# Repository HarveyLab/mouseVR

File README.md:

# Harvey Lab Mouse VR
Developed by members of the Harvey Lab (http://harveylab.hms.harvard.edu/) and the HMS Research Instrumentation Core (http://instrumentation.hms.harvard.edu/). Community contributions to any aspects of the designs or documentation very welcome, please submit a pull request with a clear description of the changes/additions and the rationale behind them.

## Table of Contents

1. [Overview](#overview)
2. [Main Components](#main-components)
3. [Getting started](#getting-started)
4. [Build Guide](#build-guide)
5. [Screen Assembly](#screen-assembly)
6. [Ball Cup Assembly](#ball-cup-assembly)
7. [Ball Sensor Software](#ball-sensor-software)
8. [Reward system](#reward-system)
9. [Behavior PCB Overview](#behavior-pcb-overview)
10. [Software](#software)
11. [Headfixation](#headfixation)
12. [FAQs](#faqs)
13. [Appendix](#appendix)

## Overview

### Main components
Harvey Lab miniaturized mouse VR rig for virtual navigation and decision-making tasks

The VR setup is comprised of several independent assemblies:

1. **The screen assembly:** a laser projector projects onto a parabolic screen surrounding the mouse. This is the basis for the visual virtual reality.

2. **Ball cup assembly:** an air-supported 8" styrofoam ball that the mouse can run on, with associated ball cup, sensors, and electronics

3. **Reward delivery system and lick sensor:** lick spout, liquid reward reservoir, solenoid, and associated electronics

4. **Enclosure:** A box surrounding the behavioral setup.

Each of these components is independent of the others: i.e. just the screen could be used in combination with a different treadmill and reward delivery system. The electronics for the ball sensors, reward delivery, and lick detection are all mounted on the same PCB. If only one or two of these functions are needed, you do not need to populate the entire PCB.

The screen assembly is designed to be small enough to be mounted within a standard 19" server rack, which could easily fit 3 rigs stacked vertically (or two + monitor and keyboard station). 

Screen and ball cup assemblies:

### Getting started

All the parts for the assemblies are listed in this google sheet: https://docs.google.com/spreadsheets/d/1hkXaeRBd7GJPuhIFjeKkEIziQik9mlkZpzjhxGrkA7A/edit?usp=sharing 

The build guide (below) contains detailed schematics of the various assemblies, **as well as additional notes about part requirements and alternative parts**. 

### Getting help

Open an issue. We will do our best to support hardware-related issues and correct errors or update documentation where things are unclear. Issues related to the design and execution of virtual environments (for example running ViRMEn code) is currently beyond the scope of this repository. 

### Contributing

We welcome contributions including, but not limited to, hardware improvements, example code for hardware interfacing, and refinements to our documentation. Please submit your contributions through a pull request.

# Build Guide

## Projector

Update 2021-02-18: 

This back projection screen assembly was originally designed for use with the Celluon Picobit laser projector (released in 2016). This projector (along with our recommended alternative laser projectors) has been discontinued and Celluon no longer produces laser projectors. The advantage of laser projectors is that they can project onto a curved surfaces with the image in focus across the entire surface. We can no longer recommend these however due to their inavailability.

We now recommend using the Texas instruments LightCrafter DLP 3010 EVM:  https://www.ti.com/tool/DLPDLCR3010EVM-G2. The DLP 2010 may also work. The back-projection enclosure has now been adapted for the DLP 3010, with a 3D-printed part holding the projector at a downward angle above the top acrylic piece to account for the upward projection angle. See the acrylic design files suffixed with "DLP_mount" and the "DLP_mount_quarter20" Inventor and STL files for the 3D-printed part, which can be mounted on the top acrylic piece with two 1/4-20 screws.

**Note 1**: The side acrylic pieces in vrRig_laserCutter_allParts_DLP_mount are also modified - they are 2 inches shorter than in the original design, and the slots for the mirrors are moved (only in the y direction). 

**Note 2**: You may have to widen the slot in the 3D-printed part by a fraction of a millimeter to account for projector manufacturing errors. The total width should be 0.4 mm wider than the width of the projector base. The design width of the base is 135.0 mm; you can measure yours with a caliper. If it fits correctly, the projector should slide in under the lips such that it is flat against the base and flush with the back of the mount.

The LightCrafters will be supported for longer than typical consumer projectors, have greater programmability, and have some some nice user features such as the ability to easily display calibration images and independently shut off Red green and blue LEDs in the software, which could be great for imaging applications - getting rid of that hard-to-block red light without a filter. Some groups have also added LEDs of desired wavelength - for example UV (this was using DLP3010). They also have fairly low input lag: from coarse tests it appears to be comparable to a standard dell desktop monitor (5-15 ms), although if this is important for you please conduct your own tests. 

The differences in focus across the screen are fairly subtle even to the human eye, so we do not expect this to impact visually-guided navigation or studies of mouse visual responses. Please see appendix for pictures of a modified screen assembly used with a DLP3010 (Oleksandr Radomskyi, Santiagio Rompani Group, EMBL, Rome). 

Thanks to Oleksandr Radomskyi and Santiagio Rompani for sharing information about using Lightcrafters with these designs. 

OLD INFO - see update above:

The projector should be a laser projector so that the image is in focus across the entire curvature of the screen. In terms of laser projectors compatible with this design, we like the Celluon PicoPro, Celluon PicoBit, or the LaserBeamPro (in that order of preference). The LaserBeamPro can exhibit burn-in.
Avoid the Sony portable laser projector due to lag. The projector throw ratio matters: get one with 1.4:1 (pretty standard for
the small laser projectors). Projectors with greater divergence will work as well. Get a projector that projects straight out i.e.
the light for the horizontal center line of the projected image should be at the same elevation as the body of the projector.
Some projectors (especially short throw) are designed to project upwards from a table or desk, this will not work with the
setup.

If you wish to use DLP projectors, we've done some basic testing of them but have not trained mice with them. The image is slightly out of focus in certain places, but it is not a serious issue. The main issue with DLP projectors is that most do not project straight out of the projector - they project slightly upwards with build in keystone correction. This has two main effects. First, the projector will need to be mounted at a slight angle relative to the top piece of the VR setup (ask Noah if this isn't clear). Second, due to the keystone correct and the angle of mounting, the transformation functions will need to be adjusted appropriately within whatever VR software you are using (if you wish to know exactly where on the screen things are being displayed). The MEX-file `fliptransform_parab_dlp_w_offset` provided under `Software/Virmen/transformations` may work for this purpose.

**Note that the laser cut mount for the projector included in these designs is specifically for the PicoBit.** It will also work with the PicoPro and laser beam pro if you remove the top "alignment" piece and stick the projector to the bottom piece using double sided tape or velcro (the height and geometry works, you will just need to center the image by eye when you stick down the projector). 

If you want to test out a DLP projection with this design, this projector: https://www.amazon.com/dp/B078PC1QS5/ref=sspa_dk_detail_5?psc=1 has the right throw. I'm not sure if it projectes straight out from the projector or slightly upwards. Parts of the projected image will be out of focus due to projecting onto a curved surface, but this might not be so bad for the mouse. If you do try it, let us know how it works!

## Screen Assembly

### Parts list and notes

The parts are listed in the "screen assembly" section of the parts list google doc: https://docs.google.com/spreadsheets/d/1hkXaeRBd7GJPuhIFjeKkEIziQik9mlkZpzjhxGrkA7A/edit?usp=sharing 

#### Mirrors

These should be approximately 1/4" thick and first surface if possible. Non first surface mirrors will result in some double
image "ghosting" but otherwise will work with the design. Acrylic mirrors can be used to save money and time - these can
easily be laser cut. Note that acrylic mirrors typically do not have surfaces as smooth as glass and the projected image may
appear textured as a result.

#### Rails, brackets, and t-nuts

McMaster or Thorlabs or any other 80-20 style rail materials should work. Note that Mcmaster t-nuts / fasteners are not
compatible with thorlabs rails as they have slightly different slot dimensions. Thorlabs t-nuts are compatible with McMaster t-slotted framing. Only the 15" Horizontal rails need to be 1/4-20 end tapped.

#### Acrylic

Any 1/4" acrylic that can be easily laser cut should work fine. It does not need to be matte or black. Opaque acrylic is best to block stray light. Stray light and reflections can also be blocked on any type of acylic using pieces of the black flocked self adhesive paper 

### Part Preparation

These steps will take approximately one hour.

For part preparation you will need the following equipment:

• Power drill

• 1/4-20 thread cutting tap

• Laser cutter with at least 12 x 24" bead, power to cut through 1/4 inch acrylic. (There are online services that will do this cutting for you if you don't have access to a laser cutter. We've been quoted around $400 for cutting these designs, although there may be cheaper options).

Steps:
**1. Laser cut the parts.** The file you should need is https://github.com/HarveyLab/mouseVR/blob/master/Hardware/BackProjection/vrRig_laserCutter_allParts.pdf. (NOTE: for the DLP 3010 projector, use https://github.com/HarveyLab/mouseVR/blob/master/Hardware/BackProjection/vrRig_laserCutter_allParts_DLP_mount.pdf instead.) The scale in the document should be 1:1, inch units, but a small 1x1" scale square is included. Ensure that it is 1" on each side, and scale parts uniformly if necessary. Arrange the parts for cutting. eg, for cutting on two 18 x 32" pieces of acrylic:

**2. Tap holes in the laser cut parts.** All round holes in the laser cut parts are either 0.26" through holes, or 0.2-0.21 holes
that should be 1/4-20 tapped. It is safe to assume that if a 1/4-20 screw does not fit through it, it should be tapped. Refer
to the parts drawings if you are unsure. Don’t worry about tapping perfectly perpendicular to the face of the acrylic - we
use a hand drill and eyeball it and that works fine for us. Use a blade to clear out waste acrylic from the parabola-shaped
screen slots in the top and bottom pieces.

**3. Cut screen film to size:** Using a ruler and a pair of scissors, cut out a rectangular piece that is approximately 21.3 x 12
inches.

4. If using McMaster rails or 80-20 that needs to be cut to length, cut 4 pieces 18" in length for the legs, and 2 pieces 15"
in length for the cross braces. Hand tap the ends of 15" pieces with the 1/4-20 thread cutting tap.

**5. If using self-adhesive black flocked paper, cut two ~ 7.5 x 4" pieces.**

### Assembly

Assembly takes approximately one hour.

Refer to the figure below for a visual guide.

Steps:

**1. Add corner brackets to the bottom piece.** Place the bottom piece (parabolic screen slot, no holes or cutout in center) flat on the table and screw four 1" brackets into it as illustrated using 3/8"-long low profile screws.

**2. Attach sides** using the 1" brackets and 3/8"-long low profile screws. The long flat edges of the sides should be on
the bottom. Stick the cut black-flocked paper / felt pieces to the inside of the sides closest to the screen. Attach four
more 1" brackets as illustrated.

**3. Attach top piece.** Screw into place from the inside using the 1" brackets and 3/8"-long low profile screws.

**4. Assemble the projector mount.** To make sure that you aren’t messing it up, screw the
projector onto the larger of the two pieces using a 3/8"-long 1/4-20 screw through the center hole in the base mount into
the threaded hole on the bottom of the projector. Make sure it is in the orientation such that the fan on the bottom of
the projector is fully visible through the cutout in the acrylic (you may need to flip the acrylic base over). Screw the top
piece of the mount into place as illustrated and then attach the entire thing to the screen assembly using 1/2" (or longer)
1/4-20 screws.

**5. Join the two sides with the end-tapped 15" rails.** Ensure that you are using the right holes and not the holes reserved for
the legs (arranged in vertical pairs 1" apart).

**6. Flip the assembly over. Insert each leg into place**, attaching it to the inside of the assembly using t-nuts or fasteners (see
this note). **Set the height of the screen by adjusting the length that each leg sticks out of the box.**
Attach the right angle brackets to the base of each leg using t-nuts /fasteners.

**7. Repeat for all four legs.** Use a ruler or measuring tape to ensure that all legs are the same height.

**8. If using the acrylic base, attach to the right angle brackets** using 3/8"-long low profile screws. The part of the base that
connects the two sides should be at the back of the assembly, away from the screen.

**9. Flip the assembly upright.** If you are assembling in its final position, bolt the screen assembly down to a breadboard or
air table and insert the two mirrors. Put tape of pieces of black flocked adhesive paper over the openings in the sides to
prevent the mirrors from slipping out. **CRITICAL STEP: the glass first surface mirrors come with a blue protective film
on the coated side. Remove this film and ensure that the coated side ("first surface") is facing towards the screen.** Both
sides will appear reflective but only one side has the reflective coating.
If you plan on moving the assembly, skip this step and insert the mirrors once it is in its final position.

**10. Slide the screen into the parabola-shaped slots.** If it does not fit, there may be waste acrylic stuck in these slots - this
can be easily removed with a box cutter or other blade. cutting a slight V into one of the horizontal edges of the screen
can help with insertion. Once the screen is in place, use binder clips, tape, or glue along the top edge to secure it. Trim away excess screen. We also often apply black tape along the vertical edges of the screen to stick it
to the sides of the box and block out stray light from the projector.

## Ball cup assembly

### Parts list and notes

The parts are listed in the "screen assembly" section of the parts list google doc: https://docs.google.com/spreadsheets/d/1hkXaeRBd7GJPuhIFjeKkEIziQik9mlkZpzjhxGrkA7A/edit?usp=sharing 

#### 3D printed ball cup
The ball cup (https://github.com/HarveyLab/mouseVR/blob/master/Hardware/BallCupAssembly/harvey_ballCup_ADNS9800_Vers1_1.ipt) should ideally be printed from a strong plastic that has good chemical resistance and can be easily cleaned. 

We get ours 3D printed by 3Dsystems using the follow specifications:

Process: Selective Laser Sintering (SLS)

Part: https://github.com/HarveyLab/mouseVR/blob/master/Hardware/BallCupAssembly/harvey_ballCup_ADNS9800_Vers1_1.ipt

Material: Glass-filled Nylon (Duraform GF)

Finish: Standard (Coated). Liquid proof entire part with cyanacrylate. Inside of the cup should eb extra smooth. 

Unit price: ~800 USD (prices vary depending on quantity).

These are expensive but work very reliably in our hadns, can be easily cleaned, and have never needed to be replaced even after years of use. 

If you do wish to use a cheaper material and/or printing technology, rigidity - specifically resistance to warping over time - is the most important material charachteristic. My guess is that ABS or a stiff nylon would work. Good chemical resistivity is recommended but not absolutely required. It is good practice to clean the ball cup regularly. Most prosumer or professional FDM, SLA, or SLS 3D printers should provide sufficient resultion for this part. The inside of the ball cup should be as smooth as possible, so lower quality printers may work as well together with some post processing such as sanding or solvent smoothing on the inside of the cup.

See FAQs for more details.

### 3D printed ball cup base

The ball cup base (https://github.com/HarveyLab/mouseVR/blob/master/Hardware/BallCupAssembly/low_profile_noiseAttachment.ipt) does not require as tight tolerances, surface finish, or chemical resistance. We get ours printed in house and probably any material is fine.  

#### Styrofoam ball
The ball cup is designed for an 8" stryrofoam ball. You can buy these on amazon or at most craft stores, but the tolerances will not be great. https://www.wecutfoam.com/ may offer slightly higher quality balls. We lathe our our 8" balls from open cell styrofoam blocks.

### Hardware Assembly

Follow these steps to assemble the sensors:

1. Sand down the back of a blue connector so that it ﬁts into the sensor board in the orientation shown in the picture below (notch in blue plastic should face away from center of board).

2. Solder the connector onto the board

3. Attach the plastic lens to the sensor board with epoxy. Apply epoxy only to the back of the board, where the small pins of the lens assembly protrude through the holes in the board. While the epoxy hardens, place the sensor lens-down on a ﬂat surface to ensure that the lens assembly is seated correctly.

4. Use a 2-56 tap to tap the screw holes in the ball cup. Alternately, just use a 2-56 screw to self-tap.

5. Put the sensors into the holes in the ball cup (oriented such that the connector pins ﬁt into the cutaway next to the sensor hole). Make sure that the sensor "slots in" all the way and sits ﬂush with the ball cup. Any failure to make the sensor completely ﬂat/tangent to cup surface will lead to erroneous measurements. Fix in place with the screws.

6. Make ribbon cables to attach the sensors to the board. Do this by cutting lengths of ribbon cable and press fitting the connectors into the ribbon cable using a vice. Secure both sides of the connectors with the included clips. **Make sure that the orientation of the connectors with respect to the colored edge of the cable is the same on both ends.** Double check with a multimeter. 

7. In the the base, file down a small notch for the ribbon cable to exit along the edge where the cup and base meet. 

8. Orient the ball cup so that one sensor is behind the mouse (it doesn’t really matter which axis is which but it is good to be consistent across rigs).

9. Screw the thorlabs posts and post holders in place on either side of the base, and bolt down the ball using 8-32 screws. Adjust the height of the posts so that the ball cup sits firm and snug on the base. Once you've tested everything, you can put a piece of electrical tape around the seam to make it more air-tight. 

10. Attach the air supply. Screw the duct hose fittings onto each end of the duct hose. Place the rubber stopper into one duct hose fitting and slide the other duct hose fitting onto the attachment point in the base (it should fit tightly). Connect the rubber stopper end of the duct hose to pressurized air using 1/4" tubing. It can be useful to have a pressure gauge & regulator between the wall air and the duct hose, as well as an air filter. You should have at least 4 feet of duct hose in order for the ball to float properly. Add more duct hose to dampen the sound.  

11. Populate the the behavior circuit board. Refer to the behavior PCB section of the guide. At the very least, you need the teensy and the ribbon cable headers. If you want an analog ball signal (as opposed to reading it directly from the teensy) you will also need the RC smoothing circuit (smoothing PWM output of the teensy) and whatever header(s) you will use to read that out (National instruments or BNC).

.

### Ball sensor software

1. Download this repo (all files required): https://github.com/HarveyLab/SPI_Mouse_Control/tree/master

2. Install the Arduino IDE and Teensyduino. Note that software will not work for all versions of Arduino IDE and Teensyduino (confirmed does not work with latest arduino/teensyduino as of April 2018 - it will compile and run but give erroneous output). An installer for verified working versions  (Arduino 1.8.2, Teensyduino 1.36) is located here: https://github.com/HarveyLab/mouseVR/tree/master/Software/BallSensor. It is highly recommended you use these versions. 

3. Connect the teensy via USB, and make sure you can identify it in the arduino software. If you are unsure at this step, read documentation and/or use trial code available from teensyduino (documentation: https://www.pjrc.com/teensy/td_usage.html)

4. Locate the debugMode.ino file in the repo (in dual-sensor) and open it. Be sure the 'ADNS9800_SROM' file is in the same folder (i.e. don't change the location of these files from how it is in repo).

5. Open the serial monitor (be sure to monitor the com port your teensy is using), and then verify/upload the code

6. As the teensy reboots, it will print information over the serial port. Verify that the 'Product ID' for both chip 1 and chip 2 is 0x33 (hexadecimal) or 51 (decimal). See images of expected output, below. If it is not, there is a low-level problem with teensy to sensor communication, usually due to incorrect wiring: immediately unplug teensy from USB to prevent sensor burn-out and review entire wiring setup to be sure pin/cable orientation is not accidentally flipped. If correct product ID is observed, proceed...

7. After booting up, the teensy will continue to live-print various information over the serial port, including the Product ID (should be constant, indicates if connection is valid), a temporally-integrated measure of velocity on pitch, roll, and yaw axes, and indicators of the image quality received by both sensors ('Squal' 1 & 2, see ADNS9800 manual included in repo for more information).

8. Verify by rotating the ball that the correct axis of rotation is inferred from the sensor (errors here usually indicate accidentally swapping Chip 1 & 2), and that the image quality from both sensors is reasonable and of similar level.

9. Once debugging is complete, locate and open the quietOp.ino file from the dual-sensor folder of repo, and verify/upload the code as before. This code will print out information over the serial port at chip boot-up only, and is preferred for running the circuit when not actively debugging. Once this code has been uploaded and the chip has rebooted the first time, the teensy will automatically re-load this program whenever it is dis-/re-connected from a power source.

Note, the discretization-resolution of the sensors can be controlled by modifying lines 116 & 121 of quietOp.ino. This involves a trade-off between the dynamic range of the PWM-channel and the smallest-detectable movement, and is set to default at 0x10 (range 0x01 - 0x29). Be sure any modification is applied to both chips equally, or rotational axes will no longer be properly de-mixed.

Expected output from debugMode.ino upon startup:

Example expected output of debugMode.ino for stationary ball:

intP,R,and Y are the pitch, roll, and yaw values. 

## Reward system

Picture of populated solenoid valve circuit:

### Lick detection circuit

Use the same  connector (to plug into PCB) and wire as the solenoid valve circuitry, but on the lick spout end, strip both red and black (ground) wires. The red wire will be connected to the lick spout and the black wire should be electrically continuous with the mouse. 

Red wire to lick spout assembly: 
Wrap the stripped end of the red wire around a section of the metal lick spout and secure it in place using either tape, zip tie, and/or heat shrink tubing. Basically it just needs to be continuous with the metal of the lick spout - this can be checked with a multimeter. Ensure that the lick spout is mounted such that it is not connected to ground or electrically continuous with any large metal pieces (like thorlabs posts and clamps, for example). This can be achieved using electrical tape or heat shrink tubing as insulation and/or plastic luer lock connectors that lick spout is screwed in to. For example, you can screw the base of the lick spout into a plastic luer lock connector with barb for reward tubing and clamp the whole thing into thorlabs SWC,RA90 or similar using a 1/4-20 screw. 

Black wire to mouse:
Attach the black wire to whatever is being used to hold the mouse's headplate. I screw it into our headplate holder (happy to share designs if you need that). You just need to be electrically continuous with the mouse with low resistance. 

Test the lick detector:
I do this with my hand: put one finger on the headplate holder and with another on the same hand touch the lick spout. Lick detector circuit output should be high when you are touching it (i.e. connecting spout and ground), low otherwise.

Note: do not assume that if you are electrically continuous with the headplate then you are continuous with the mouse. This might not be the case depending on your surgical prep. If you are getting poor lick detection through the mouse but the lick detector is working perfectly when you test it (i.e. with your hand as described above) then it is possible that the mouse is not properly grounded. This can be easily remedied by placing a drop of ultrasound gel touching both the headplate and the mouse's skin (I sometimes would put it behind one ear) - that has always been sufficient in my hands to bridge the mouse to ground. 

## Behavior PCB Overview

The behavior PCB has the circutry to monitor two lick inputs (for example if using lick left / lick right setup), control two independent solenoid valves for dispensing liquid reward, and interface with ball movement sensors. 

You can read sensors and control valves using **(a)** the teensy directly (with serial communication) **(b)** a USB-3001 NIDAQ plugged into the board **(c)** some combination of the teensy and the NIDAQ. 

Note in the photo of the populated board the MOSFETs in the reward circuit are not pictured. Refer to "Reward Circuit" for an image of the populated circuit on that section of the board. https://github.com/HarveyLab/mouseVR/tree/master/BehaviorElectronics contains complete schematics and bill of materials, so it is best to use those as a guide when populating your board. 

**Options for reading in licks:**
1. Read in licks as an analog signal exactly like the ball signal. Note you may miss licks this way if your sampling rate is low.
2. Attach the lick output to a counter channel on your DAQ & read the counter channel (not sure if these boards are capable of having counter channels or not) http://www.ni.com/academic/students/learn-daq/digital/ 
3. Set up a counter on the teensy and read directly from the teensy using serial communication

**Options for controlling reward valve:**
1. Control using the DAQ analog output (User 3 and/or 4). Set duration of valve opening in your matlab code (e.e. write a giveReward function). You wil need to install jumpers (see fig below) if you haven't already. 
2. Control using teensy triggered by DAQ (User 3 and/or 4, always accesible to teensy, even w/out jumpers present)
3. Control using teensy triggered by serial communication

NIDAQ connections

### Getting started

The parts are listed in the "behavior electronics" section of the parts list google doc: https://docs.google.com/spreadsheets/d/1hkXaeRBd7GJPuhIFjeKkEIziQik9mlkZpzjhxGrkA7A/edit?usp=sharing 

The files to get the circuit board printed are in https://github.com/HarveyLab/mouseVR/tree/master/BehaviorElectronics/HarveyBehaviorPCB_v1.2 
We use 4pcb.com 

The top will be screen printed with parts codes that you can look up in the bill of materials here: 
https://github.com/HarveyLab/mouseVR/blob/master/BehaviorElectronics/HarveyBehaviorPCB_v1.2_BOM.xlsx

Also refer to the board schematic here:
https://github.com/HarveyLab/mouseVR/blob/master/BehaviorElectronics/HarveyBehaviorPCB_v1.2.pdf

Final board should look like this:

# VR rig details

Mouse positioning relative to the screen:

You can place the mouse further back to allow for more room for equipment and this seems to be fine for behavior. 

Very approximate visual field coverage with the placement of the mouse as above:

# Software

## ViRMEn transformation functions
We use the ViRMEn virtual reality engine: https://pni.princeton.edu/pni-software-tools/virmen.  

https://github.com/HarveyLab/mouseVR/blob/master/Software/Virmen/transformations/fliptransformCyl_NPparab.m Is an example of a ViRMEn transformation function that works reasonably well with this setup. It isn't the most accurate but looks fairly good to me and I've had good mouse behavior. Some people have approximated the parabola as a cylinder which can speed things up. If you're doing something that requires knowing exactly where in the visual field something is presented, don't rely on this function.

For the DLP lightcrafter build contributed by Ethan, there is are transformations functions in https://github.com/HarveyLab/mouseVR/tree/master/Software/Virmen/transformations.

# Headfixation

Head-fixation harware is somewhat is independent of the VR setup, but here are some designs for headplates and headplate holders developed in the Harvey lab for our experiments.  

Design files are in: https://github.com/HarveyLab/mouseVR/tree/master/Hardware/HeadplatesAndHolders  

## Headplates

All of the following headplates are designed to be cut from ~0.04" titanium. Waterjet cutting arguably produces the smoothest edges but the easiset and fastest service for getting them made is sendcutsend.com. 100 headplates will cost ~$130 and each can be reused many times. For ordering, upload a dxf file (either one in this repository, or export from inventor by right-clicking the face of the part and selecting "export face as...") and select Grade 5 Titanium (.040") as the material. 

All units are by default inches.

### headplate_largerCenter
This is the "standard" headplate using the harvey lab. It is called "larger center" because the opening int he middle has been expanded from older versions to accomodate larger cranial windows. 

### headplate_largerCenter_frontcutout
Modified from headplate_largerCenter to have the front cut out. This was designed for CA1 imaging to allow the headplate to be placed much closer to the skull to give enough working distance for the objective to image through a cannula. It alos provides a bit more flexibility to in terms of headplate positioning relative to the window.

### headplate_largerCenter_frontsidecutout
Modified from headplate_largerCenter to have the front cut and side cutout. One clamping fork was removed for better positioning during ca1 surgery. In conjuction with the two-sided headplate holder, fixation is very stable (e.g. for 2p imaging, no vibrations or motion outside of normal brain motion) and highly reproducible across days (~on the order of a few tens of microns).

### harveyLabWideHeadplate_1p4in
Version with longer forks coming out side

## Headplate holders

### twoSidedHeadplateHolder_NP_v02

Designed for reproducible mounting across days, especially for pitch, roll, and yaw, which cannot be compensated for by XYZ stages.  (translation reproducibility is on the order of a few tens of microns which can be easily compensated for using the stage). Note some of the holes are for clamping screws, some are for alignment pins or set screws (more on that below).

Machined from aluminium. Small holes should be 4-40 tapped, larger holes can optionally be 1/4-20 tapped for affixing lick spout hardware. No fillet or chamfer on the edges so make sure to ask the machinist to deburr the edges. Note the fillets where the two arms become thinner are uncessesary and could just as well be steps or whatever is easier to machine. 

For imaging setups it should be milled from aluminium. For training rigs where micron-level stability is not needed, 3d printed or laser cut plastic is ok. 1/8 inch acrylic will flex and vibrate a bit but I have still used it to train mice and it was fine. 

I recommend using these screws for attaching the headplate:
https://www.mcmaster.com/98164A429/
Shorter screws (1/8") will work too but will wear out the threads in the headplate holder faster. 

These set screws should be used for alignment:
https://www.mcmaster.com/92311A105/

Here is the configuration I of screws I have used:

Set screws in the alignment holes can be used to provide 3 points of contact between the edges of the headplate and the holder, thus providing reproducible mounting to within a few tens of microns, and constraining rotational degrees of freedom. The arrow indicates the direction of force I apply to the headplate while clamping it in place. I usually clamp in place with screws in clamping holes 3 and 1, or 2 and 3, or Clamping hole 2 and Alignment hole 3, but you can experiment with what works well for you. The unlabelled holes can be used to store screws - for example if clamping with holes 2 and 3 - one of the screws will need to be moved into place one the headplate is in position. 

It is designed to be mounted to this kinematic plate from thorlabs: https://www.thorlabs.com/thorproduct.cfm?partnumber=KB3X3

I mount the kinematic plate and headplate holder to this https://www.thorlabs.com/thorproduct.cfm?partnumber=C1515 for use with a 1.5 inch post for imaging.

I used these damped posts but they are probably overkill, any 1.5" post would do. https://www.thorlabs.com/newgrouppage9.cfm?objectgroup_id=170. 

The kinematic mount allows for the headplate holder to be removed for cleaning the ball and cup and put back in place in the exact same position. 

The mounting can be easily customized but having it on a kinematic base allows you to maintain reproducible positioning while also being able to remove the headplate holder to clean and remove the ball and access ball cup. I suggest while the mouse is on there to use a single long screw through the center hole of the kinematic base into C1515 bracket (finger-tight) to ensure everything is fixed in place, since the magnets of the kinematic base are not super strong.  

### twoSidedHeadplateHolder_wide_sendcutsend and twoSidedHeadplateHolder_v3_scs.dxf

A version designed to be cut by sendcutsend.com from a flat sheet of stainless steel. Each one costs about $80, which is cheaper than getting the aluminum one machined. Another advantage is that the 4-40 hole threads are prone to wear out over time and this happens quite a lot more slowly with steel. The disadvantage is that the material is a bit thicker and send-cut-sent dimensional accuracy does not quite match CNC machining. To place an order: Upload twoSidedHeadplateHolder_v3_scs.dxf and choose material Stainless Steel (304 series) (.125"). Select 4-40 tapping for smaller holes and 1/4-20 tapping for larger holes. It is possible that thinner versions of stainless steel would work as well but we have not tested those.  This design has more holes than the other headplate holder in order to accomodate ever wider headplate designs (such as harveylabwideheadplate_1p4in.dxf). However it should be backwards compatible with all the headplates listed here. 

# FAQs

## What are the computer hardware requirements?
The projector is driven simply as another monitor, so this really depends on the VR software that you are using and the complexity of the worlds that you need to render. Consult the documentation for whatever visual stimulus or VR software you are using: Our computers use GTX 1060 cards (https://www.amazon.com/GR8-II-T044Z-Desktop-i5-7400-GeForce/dp/B06WLHT15C is one model we have used successfully) but this is overkill for most of the worlds we render. Integrated graphics are a bad idea and will likely result in <60FPS. For ViRMEn we suggest at least a 3.00GHz CPU and 8GB of RAM. 

## What are the pros and cons of using this setup over multiple monitors?
The pros (+) and cons (-) of multiple monitors:

(+) slightly better availability and choice of different screen types and resolutions. may be better if you care about precise visual stimulus timing as gaming monitors are available w/ high frame rates and low input lag.

(+) Potential to be more compact (although this design is already very compact).

(-) Requires either better graphics card to drive 3+ monitors or additional hardware such as "triple head-to-go" (which may complicate transformation functions and introduce lag - you'd need to test). 

(-) Bezels: not a big deal for navigation stuff, but does disrupt things like whole-field optic flow, visual RF mapping in same experiment, etc. May be less immersive.

(-) May be harder to correct for illumination across visual field as that can vary w/ angle that the mouse is seeing the screen from.

(-) Less flexible configuration - with our design you can cut holes, notches, slots into any part of the screen etc to fit optics, microscopes, cameras, etc. You can easily resize the screen and adjust design. We have found this to be very useful.

The projector also has the advantage that it's easy to apply filters to the output of the projector. For example: dimming the brightness uniformly with an ND filter, or applying a short-pass filter to attenuate hard-to-light-block red wavelengths (that the mouse can't see anyway) during imaging experiments. 

We have used both a 3 monitor setup and this design and have not found a difference in terms of behavior.

## Many of these parts are expensive for our lab - are there cheaper alternatives?

In many cases there are cheaper alternatives. Some of these are listed in the parts list. 

For example:

Ball cup: May be printed with cheaper materials / quality than the quote listed. We have not explored this. See ball cup section in this guide for more details.

Projector: Low resolution DLP mini projectors are very cheap! Using different projectors may require some small modifications to the hardware. See projector section for more details. 

Thorlabs: most of these parts can be replaced with equivalents from McMaster, 80-20, amazon, etc. 

First surface mirrors: First surface mirrored acrylic is also available for much cheaper and can be laser cut. There will be a slight textured look to the projected image (due to surface not being as flat) but it is subtle and I'm pretty sure it wouldn't influence behavior. 

Acrylic: There are cheaper sources than Canal Plastics for the acrylic. It does not need to have high thickness tolerances and it does not need to be black - any color will work. 

## I want to use metric screws / hardware - are these deisgns compatible?

We haven't tested this but it should be! Use M6 screws / taps in place of 1/4-20. Please let us know if this works! Everything was desinged in inches, so if units appear undefined for a particular drawing, please assume inches.  

## How do I order the behavior PCBs

We use 4pcb.com $33 per board special: https://www.4pcb.com/pcb-prototype-2-4-layer-boards-specials.html 

1. Select 2 layer, 5 day turn

2. Sign into your account (or create one)

3. Step 1 of 4: upload files. Upload the .zip file in https://github.com/HarveyLab/mouseVR/tree/master/BehaviorElectronics

4. Part#: HarveyBehaviorPCB_v1
Rev#: 1.2
X dim(in): 8
Y dim(in) 4.95
Soldermask: both side
silkscreen: top side
layers: 2
Quantity: 10 (or whatever you want > 3)
Multiple Images: No
Ship methoid: your choice
ITAR: No

5. Enter shipping and billing info 

6. Comments: STUDENT

## How do you calibrate the ball sensors?

First, make sure that the sensors are oriented the same way as we have them and offset by 90 degrees in yaw. Make sure that the sensor sits ﬂush with the ball cup. Any failure to make the sensor completely ﬂat/tangent to cup surface will lead to erroneous measurements. Note that the part of the sensor chip with the ribbon cable socket should be towards the top of the ball! See the ball cup assembly section of the guide for more info. 

The teensy outputs velocity signals for pitch, roll, and yaw in arbitrary units. The magnitude of these readings can vary depending on a bunch of different things including (I think) the distance of the ball from the sensors. It is recommended that you somewhat regularly check calibration since the styrofoam balls naturally wear down over time and this change in size can influence the readings. It shouldn't drift by a huge amount, but better to be safe.

Calibration is very simple and we do it regularly. Hook everything up, set up your VR software and movement function, and rotate the ball by a set amount in pitch, roll, or yaw. Pitch corresponds to forward running and we typically use roll for either lateral or view angle changes. After rotating by a set amount (for example, 2 ball rotations), note the distance travelled in the virtual environment (either in view angle degrees or translational movement). Knowing the circumference of the ball (~63.8 cm), you can set gain(s) in your vr software appropriately such that you have a certain number of vr_units per cm. 

## What factors are important for mouse positioning relative to the ball and the screen?

Note that positioning on the ball and relative to the screen can be thought of as pretty much independent of each other. If you want to change the positioning relative to the screen i'd recommend moving the ball cup assembly, and not repositining the mouse relative to the ball. More about the factors that go into the positioning:

1. Positioning on the ball. This positioning has been optimized in the early days of Chris's lab for good mouse behavior and ball control. For tasks in which the mouse needs to turn/steer, we typically use roll for side-to-side translation or view angle and pitch for forward movement. If the mouse is sitting towards the top of the ball it will often result in the mouse spinning the ball mostly in yaw (it may be hard to imagine this but once you have a mouse on the ball you'll see what I mean). Placing the mouse further back on the ball increases rotation in pitch and encourages forward running. I believe steering is also aided by this slightly further-back position. If your task requires turning or steering I'd recommend starting with this position and adjusting from there. If you are just using a linear track & a yaw/roll blocker then the ball becomes a treadmill and positioning is not quite as important. 

2. Positioning relative to the screen. One factor to consider here is the focal distance of the mouse's vision. Everything beyond about 5 inches is in focus for the mouse (reference?). I'm not sure how detrimental it would be to have parts of the screen closer than this and thus out of focus. We discussed increasing the peripheral coverage when designing the VR and decided that it wasn't worth it for what we use it for. 210 deg of visual coverage is fine for behavior and we get nice place cells with it as well.
If you decide to move the ball closer to the screen, you may want to create a small cutout in the bottom of the screen so that the ball doesn't hit into it, or just raise the screen by a bit. 

# Troubleshooting

# Appendix

## Part drawings / dimensions:

### Screen assembly

### Modified screen assembly with Texas Instruments DLP3010 
From Oleksandr Radomskyi, Santiagio Rompani Group, EMBL, Rome

### Ball cup

### Ball cup base

### Enclosure

### Slide out

low profile drawer slides mounted with laser cut acrylic for pulling the ball cup assembly away from the screen in order to more easily mount the mouse and access the ball cup for cleaning. Slides should not be used with ephys or imaging due to instability and vibrations. 

Contributors: Noah Pettit, Matthias Minderer, Selmaan Chettih, Charlotte Arlt, Jim Bohnslav, Pavel Gorelick, Ofer Mazor, Christopher Harvey.

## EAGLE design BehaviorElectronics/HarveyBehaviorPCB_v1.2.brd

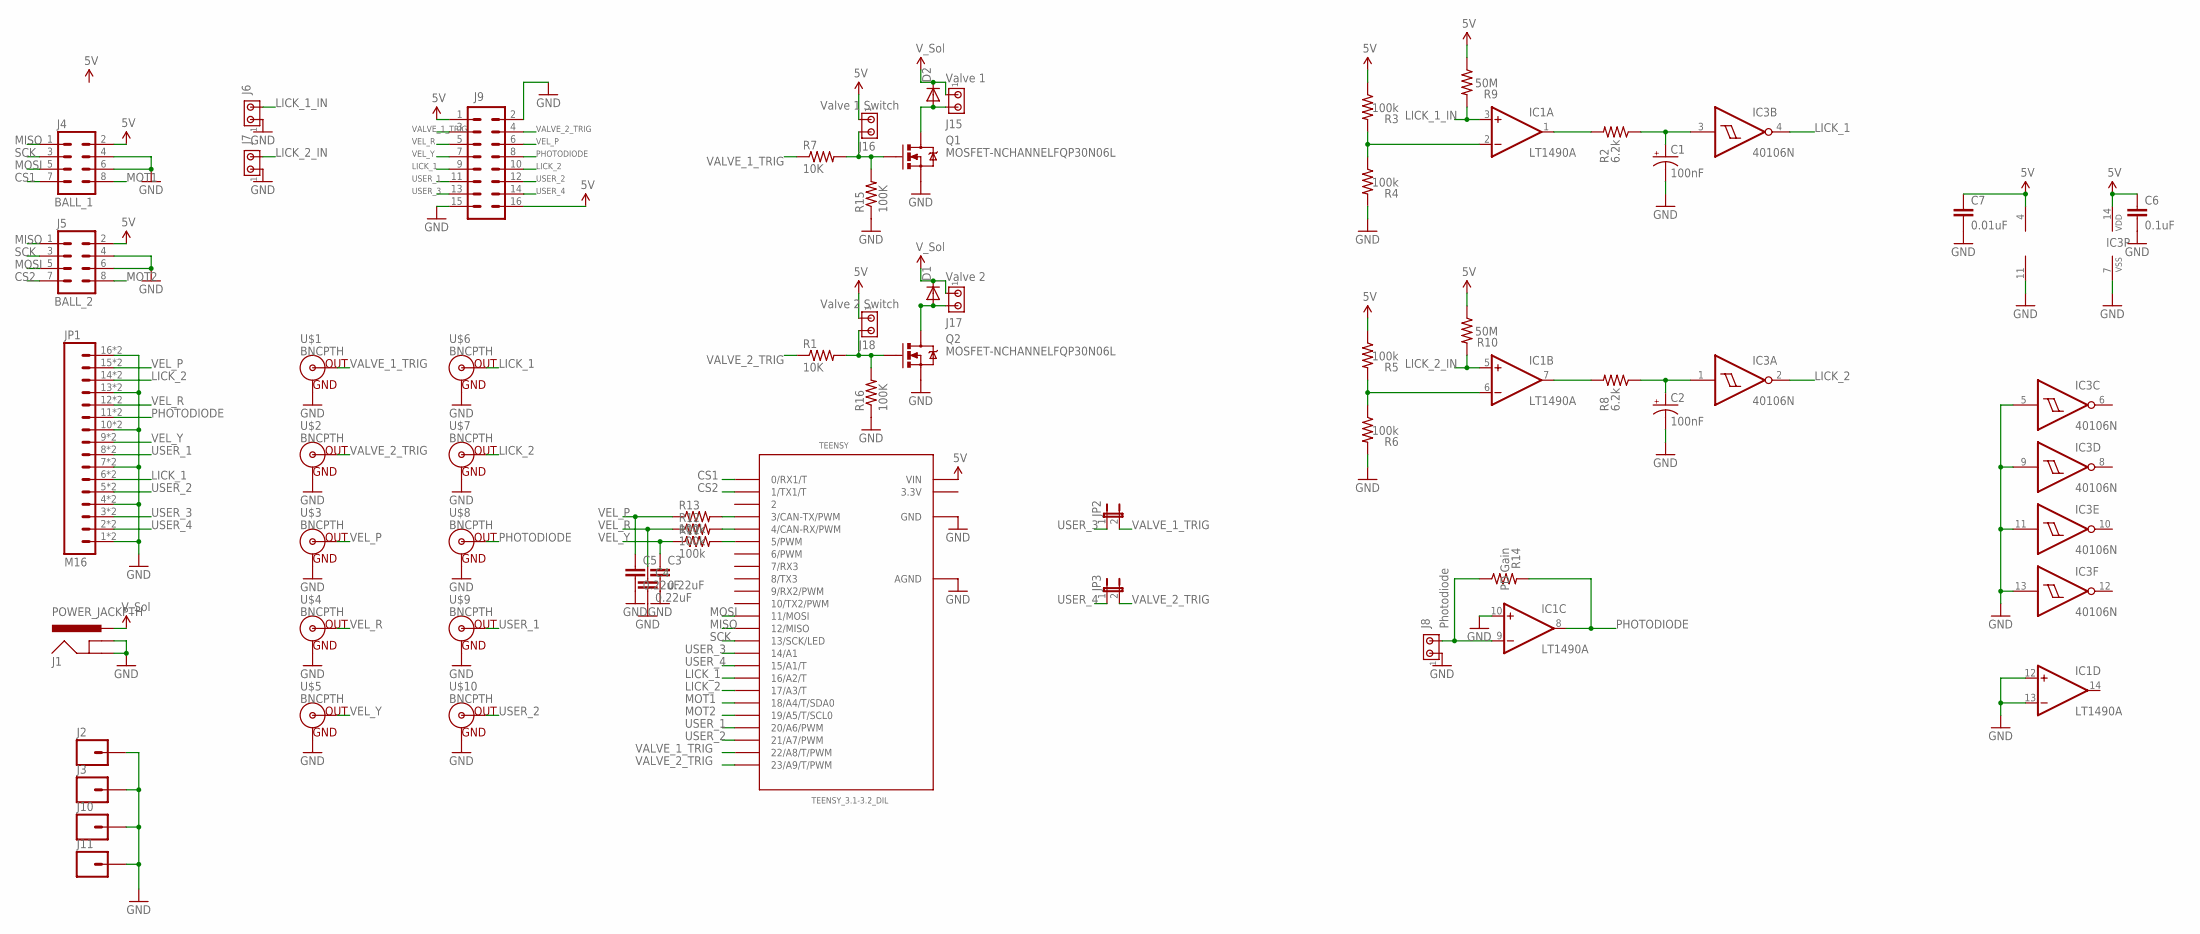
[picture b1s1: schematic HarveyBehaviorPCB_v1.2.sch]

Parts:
C1, C2: 100nF; CPOL-RADIAL-10UF-25V
C3, C4, C5: 0.22uF; CAP-PTH-SMALL2
C6: 0.1uF; CAP-PTH-SMALL-KIT
C7: 0.01uF; CAP-PTH-SMALL-KIT
D1, D2: 1N4148; DO41-10
IC1: LT1490A; DIL14
IC3: 40106N; DIL14
J1: POWER_JACKPTH; POWER_JACK_PTH
J2, J3, J10, J11: M01SMTSO-256-ET-0.165DIA; SMTSO-256-ET-0.165DIA
J4: BALL_1; 2X4
J5: BALL_2; 2X4
J6, J7: MTA02-100; 10X02MTA
J8: Photodiode; 10X02MTA
J9: M08X2; 2X8
J15: Valve 1; 10X02MTA
J16: Valve 1 Switch; 10X02MTA
J17: Valve 2; 10X02MTA
J18: Valve 2 Switch; 10X02MTA
JP1: M16; 1X16_TERM_BLOCK_0.15"
JP2, JP3: JUMPER-2PTH; 1X02
Q1, Q2: MOSFET-NCHANNELFQP30N06L; TO220V
R1, R7: 10K; AXIAL-0.5
R2, R8: 6.2k; AXIAL-0.5
R3, R4, R5, R6, R11, R12, R13: 100k; AXIAL-0.5
R9, R10: 50M; AXIAL-0.5
R14: PD Gain; AXIAL-0.5
R15, R16: 100K; AXIAL-0.5
TEENSY: TEENSY_3.1-3.2_DIL; TEENSY_3.0-3.2&LC_DIL
U$1, U$2, U$3, U$4, U$5, U$6, U$7, U$8, U$9, U$10: BNCPTH; BNC

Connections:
3.3V: TEENSY.3.3V
5V: C6.1, C7.1, IC1.4 (V+), IC3.14 (VDD), J4.2, J5.2, J9.1, J9.16, J16.1, J18.1, R3.P$1 (1), R5.P$1 (1), R9.P$1 (1), R10.P$1 (1), TEENSY.VIN
CS1: J4.7, TEENSY.0 (0/RX1/T)
CS2: J5.7, TEENSY.1 (1/TX1/T)
GND: C1.2 (-), C2.2 (-), C3.2, C4.2, C5.2, C6.2, C7.2, IC1.10 (+IN), IC1.11 (V-), IC1.12 (+IN), IC1.13 (-IN), IC3.5 (I), IC3.7 (VSS), IC3.9 (I), IC3.11 (I), IC3.13 (I), J1.GND, J1.GNDBREAK, J2.P$1, J3.P$1, J4.4, J4.6, J5.4, J5.6, J6.1, J7.1, J8.1, J9.2, J9.15, J10.P$1, J11.P$1, JP1.1, JP1.4, JP1.7, JP1.10, JP1.13, JP1.16, JP1.17 (1), JP1.20 (4), JP1.23 (7), JP1.26 (10), JP1.29 (13), JP1.32 (16), Q1.3 (S), Q2.3 (S), R4.P$2 (2), R6.P$2 (2), R15.P$1 (1), R16.P$1 (1), TEENSY.AGND, TEENSY.GND, U$1.GND, U$2.GND, U$3.GND, U$4.GND, U$5.GND, U$6.GND, U$7.GND, U$8.GND, U$9.GND, U$10.GND
LICK_1: IC3.4 (O), J9.9, JP1.6, JP1.22 (6), TEENSY.16/A2 (16/A2/T), U$6.S (OUT)
LICK_1_IN: IC1.3 (+IN), J6.2, R9.P$2 (2)
LICK_2: IC3.2 (O), J9.10, JP1.14, JP1.30 (14), TEENSY.17/A3 (17/A3/T), U$7.S (OUT)
LICK_2_IN: IC1.5 (+IN), J7.2, R10.P$2 (2)
MISO: J4.1, J5.1, TEENSY.12 (12/MISO)
MOSI: J4.5, J5.5, TEENSY.11 (11/MOSI)
MOT1: J4.8, TEENSY.18/A4 (18/A4/T/SDA0)
MOT2: J5.8, TEENSY.19/A5 (19/A5/T/SCL0)
unnamed: C1.1 (+), IC3.3 (I), R2.P$1 (1)
unnamed: IC1.1 (OUT), R2.P$2 (2)
unnamed: IC1.2 (-IN), R3.P$2 (2), R4.P$1 (1)
unnamed: D2.A, J15.2, Q1.2 (D)
unnamed: J16.2, Q1.1 (G), R7.P$2 (2), R15.P$2 (2)
unnamed: D1.A, J17.2, Q2.2 (D)
unnamed: J18.2, Q2.1 (G), R1.P$2 (2), R16.P$2 (2)
unnamed: IC1.6 (-IN), R5.P$2 (2), R6.P$1 (1)
unnamed: C2.1 (+), IC3.1 (I), R8.P$1 (1)
unnamed: IC1.7 (OUT), R8.P$2 (2)
PHOTODIODE: IC1.8 (OUT), J9.8, JP1.11, JP1.27 (11), R14.P$2 (2), U$8.S (OUT)
PHOTODIODE_IN: IC1.9 (-IN), J8.2
SCK: J4.3, J5.3, TEENSY.13 (13/SCK/LED)
USER_1: J9.11, JP1.8, JP1.24 (8), TEENSY.20/A6 (20/A6/PWM), U$9.S (OUT)
USER_2: J9.12, JP1.5, JP1.21 (5), TEENSY.21/A7 (21/A7/PWM), U$10.S (OUT)
USER_3: J9.13, JP1.3, JP1.19 (3), JP2.1, TEENSY.14/A0 (14/A1)
USER_4: J9.14, JP1.2, JP1.18 (2), JP3.1, TEENSY.15/A1 (15/A1/T)
VALVE_1_TRIG: J9.3, JP2.2, R7.P$1 (1), TEENSY.22/A8 (22/A8/T/PWM), U$1.S (OUT)
VALVE_2_TRIG: J9.4, JP3.2, R1.P$1 (1), TEENSY.23/A9 (23/A9/T/PWM), U$2.S (OUT)
VEL_P: C5.1, J9.6, JP1.15, JP1.31 (15), R13.P$1 (1), U$3.S (OUT)
VEL_P_PWM: R13.P$2 (2), TEENSY.3 (3/CAN-TX/PWM)
VEL_R: C4.1, J9.5, JP1.12, JP1.28 (12), R12.P$1 (1), U$4.S (OUT)
VEL_R_PWM: R12.P$2 (2), TEENSY.4 (4/CAN-RX/PWM)
VEL_Y: C3.1, J9.7, JP1.9, JP1.25 (9), R11.P$1 (1), U$5.S (OUT)
VEL_Y_PWM: R11.P$2 (2), TEENSY.5 (5/PWM)
VSOL: D1.C, D2.C, J1.PWR, J15.1, J17.1

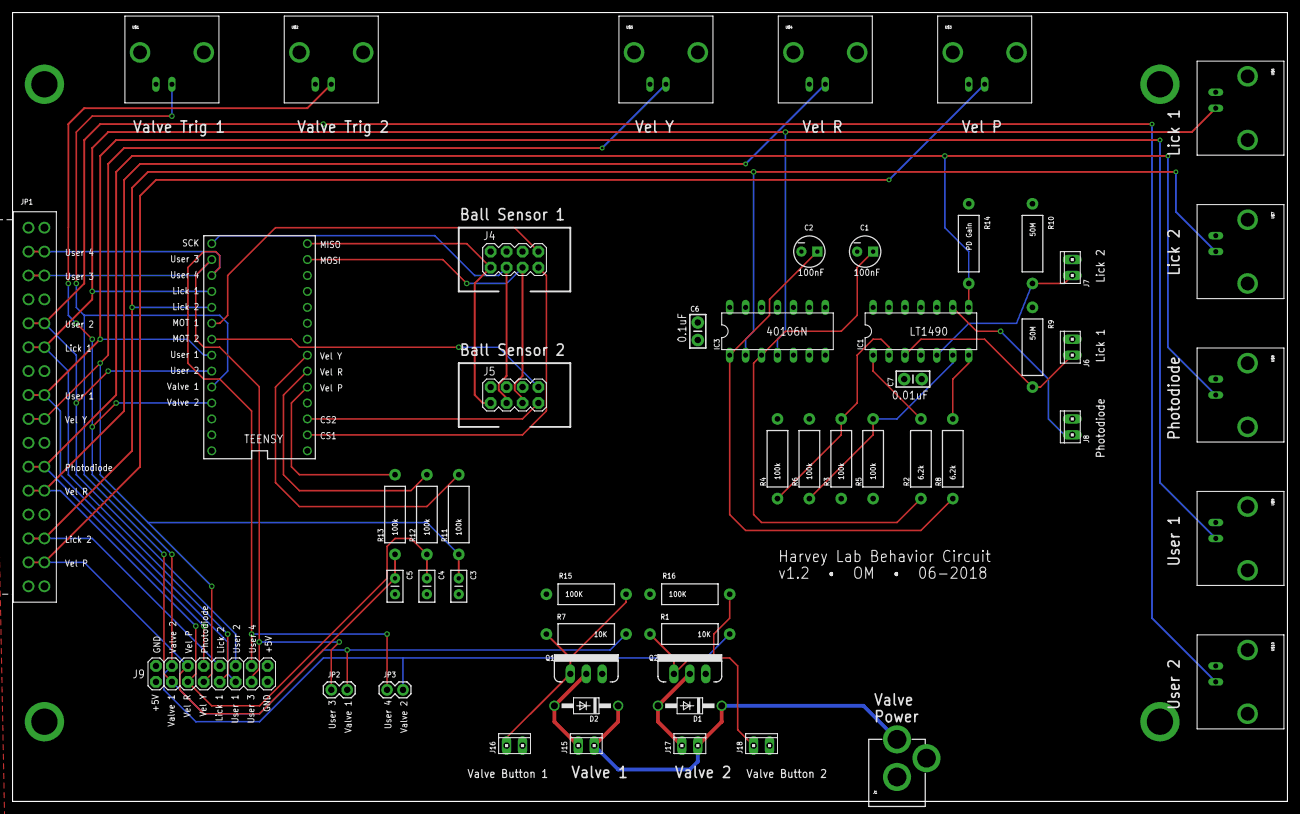
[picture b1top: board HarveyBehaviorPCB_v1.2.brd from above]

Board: 2 copper layers, 203.2 x 125.7 mm, 58 parts (0 on the bottom side), 38 nets.

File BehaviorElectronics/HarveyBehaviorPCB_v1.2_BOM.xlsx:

Part | Value | Device | Digikey Part # | Price | Description | Notes
C1 | 100nF
C2 | 100nF
C3 | 0.22uF
C4 | 0.22uF
C5 | 0.22uF
C6 | 0.1uF
C7 | 0.01uF
D1 |  | 1N58 | 497-7053-1-ND | 0.39 | DIODE
D2 |  | 1N58 | 497-7053-1-ND | 0.39 | DIODE
IC1 |  | LT1490A | LT1491ACN#PBF-ND | 6.41 | Quad OP AMP
IC3 |  | 40106 | 296-3503-5-ND | 0.51 | Hex SCHMITT TRIGGER
J1 |  | PJ-202A | CP-202A-ND | 0.61 | Power Jack | (or equivalent part)
J2 |  |  |  |  | Standoff Hole
J3 |  |  |  |  | Standoff Hole
J4 |  | Shrouded 2x4 header | 609-3530-ND | 0.76 | BALL_1
J5 |  | Shrouded 2x4 header | 609-3530-ND | 0.76 | BALL_2
J6 |  | MTA02-100 | A19423-ND | 0.11 | AMP connector
J7 |  | MTA02-100 | A19423-ND | 0.11 | AMP connector
J8 |  | MTA02-100 | A19423-ND | 0.11 | AMP connector | Photodiode
J9 |  | M08X2 | 609-3220-ND | 0.6 | .1 headers | (or equivalent part)
J10 |  |  |  |  | Standoff Hole
J11 |  |  |  |  | Standoff Hole
J15 |  | MTA02-100 | A19423-ND | 0.11 | AMP connector | Valve 1
J16 |  | MTA02-100 | A19423-ND | 0.11 | AMP connector | Valve 1 Switch
J17 |  | MTA02-100 | A19423-ND | 0.11 | AMP connector | Valve 2
J18 |  | MTA02-100 | A19423-ND | 0.11 | AMP connector | Valve 2 Switch
JP1 |  |  | 277-6221-ND | 17.34 | DAQ connector
JP2 |  |  | 952-2262-ND |  | Jumper | also need jumper cap (e.g.,S9337-ND)
JP3 |  |  | 952-2262-ND |  | Jumper | also need jumper cap (e.g.,S9337-ND)
Q1 |  |  | 568-7512-5-ND |  | N-FET
Q2 |  |  | 568-7512-5-ND |  | N-FET
R1 | 10K |  |  |  | Resistor
R2 | 6.2k |  |  |  | Resistor
R3 | 100k |  |  |  | Resistor
R4 | 100k |  |  |  | Resistor
R5 | 100k |  |  |  | Resistor
R6 | 100k |  |  |  | Resistor
R7 | 10K |  |  |  | Resistor
R8 | 6.2k |  |  |  | Resistor
R9 | 50M |  |  |  | Resistor
R10 | 50M |  |  |  | Resistor
R11 | 100k |  |  |  | Resistor
R12 | 100k |  |  |  | Resistor
R13 | 100k |  |  |  | Resistor
R14 |  |  |  |  | PD Gain Resistor | Value depends on desired photodiode gain.
R15 | 100k |  |  |  | Resistor
R16 | 100k |  |  |  | Resistor
TEENSY |  | TEENSY 3.2 |  |  | Teensy 3.1 or 3.2 in a DIL Layout.
U$1 |  |  | WM5514-ND | 1.48 | BNC Connector
U$2 |  |  | WM5514-ND | 1.48 | BNC Connector
U$3 |  |  | WM5514-ND | 1.48 | BNC Connector
U$4 |  |  | WM5514-ND | 1.48 | BNC Connector
U$5 |  |  | WM5514-ND | 1.48 | BNC Connector
U$6 |  |  | WM5514-ND | 1.48 | BNC Connector
U$7 |  |  | WM5514-ND | 1.48 | BNC Connector
U$8 |  |  | WM5514-ND | 1.48 | BNC Connector
U$9 |  |  | WM5514-ND | 1.48 | BNC Connector
U$10 |  |  | WM5514-ND | 1.48 | BNC Connector

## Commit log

2019-01-03 Added new inventor files and folder structure
2019-01-03 updated back projection files to include tapped holes and removed some uneeded holes
2019-01-04 added assembly files
2019-01-04 added docs folder
2019-01-04 added ball cup assembly parts, enclosure, slide out
2019-01-04 added some software folders and files
2019-01-04 Set theme jekyll-theme-cayman
2019-01-04 added some overview technical drawings for backprojection assembly
2019-01-08 added assemblies, build guide schematics, figures, etc
2019-01-09 added files, updated readme
2019-01-09 added overview png
2019-01-10 added parts, restructured guide folder
2019-01-10 added figure
2019-01-10 added figs
2019-01-10 fig update
2019-01-10 added files for laser cutter
2019-01-10 Added laser cutter files
2019-01-10 screen dimension figure added
2019-01-10 added ball assembly overview figure
2019-01-10 fixed typos
2019-01-10 added some photos
2019-01-14 some updated figures for instructions
2019-01-15 added some figures to guide
2019-01-17 updated documentation and parts list
2019-02-09 updated FAQ and ball cup info
2019-02-09 Added list of contributors
2019-04-15 added table of contents header links
2019-04-15 fixed anchor tag typo
2020-09-25 Create LICENSE
    added MIT License
2020-10-03 vr overview image with white background
    added screenshot of VR overview w/ white background
2021-02-18 added DLP 3010 EVM images
2021-02-18 moved dlp 3010 images to guide
2021-10-13 Changed background of pngs to white to work with github dark theme
2023-03-07 Add design files, code & documentation for DLP build
2023-03-10 Update README to clarify important info about DLP setup
2023-04-05 Update readme with lick detector spout wiring notes
2023-06-14 added headplate and headplate holder designs
2023-06-14 Update README.md to include info on headplates and holders
2023-06-14 Added dxf files of the headplates for sendcutsend
2023-06-15 Update README.md
    added note about DLP build transformation functions
2023-10-13 Update README.md
    Including image of populated reward valve circuit and note on populating PCB using schematics and BOM

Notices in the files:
parts and their libraries:
SparkFun-Connectors: Licensing: Creative Commons ShareAlike 4.0 International - https://creativecommons.org/licenses/by-sa/4.0
